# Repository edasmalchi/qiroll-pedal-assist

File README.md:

# qiroll-pedal-assist
#### External pedal-assist system for Qiroll ebike kit, implemented with CMOS digital logic

So I got this Qiroll friction-drive ebike kit  to put on my commuter bike. I'd reccomend the [pro](https://www.aliexpress.com/item/1005002975061464.html) [version](https://www.ebay.com/itm/Electric-Bicycle-E-BIKE-Conversion-Kit-QiROLL-Friction-Drive-QR-E-PRO-H70/402658347675) (about $600 shipped), but the standard [kit](https://www.aliexpress.com/item/4000366510773.html) (about $450 shipped) is still around. With light pedaling, the pro version on my bike cruises at about 23mph with about 20 miles of range, while the standard kit delivers about 19mph and about 20 miles (with the larger B70 battery).

The lack of any sort of pedal assist bothered me, with the original design you have to hold down a switch to keep the motor on. (It's a simple switch, not a real throttle so the motor is either on or off. There is a way to select between a lower power mode and a higher power mode.)

This project aims to add pedal assist functionality to the Qiroll kit. I'm using this 12-magnet pedal assist [sensor](https://smile.amazon.com/gp/product/B08GY819YF/), although similar products could work too. The project also supports an optional brake sensor, I'm using [this one](https://www.aliexpress.com/item/4000445394702.html) but others likely work as well. Be sure to verify proper operation in case yours works differently.

#### Hardware Mods
* Since my design needs only one button, with single-clicks turning pedal assist on/off and double-clicks switching controller modes (and/or enabling regen), I didn't need the second button in the original Qiroll switch. So I desoldered it, and used the space/wiring for a resistor and an led that lines up nicely with the hole left by taking the button out, letting me see if pedal assist is currently on or off!

* Stripped the insulation and soldered into one of the battery wires to tap power-- should be fine since the pedal assist system uses very little current but be careful not to damage the battery wire itself. Alternatively you could get some of those Amass connectors it uses and make an adaptor.
* Depending on your setup, cable strain at the battery connector seems to be an issue. Reccomend adding extra strain relief here, and consider tapping at the motor connection instead since splicing in another wire with solder does weaken things.

#### Notes
* The sensor I got reads in both directions, so it will trigger on backwards pedaling as well. I don't think this is a big deal, but there may be sensors out there that only read in one direction.
* After much investigation, the power from the Qiroll micro-usb switch port seems to fluctuate quite a bit. So the reliable thing to do is tap into the + side of the battery, using a linear voltage regulator (or buck converter) to drop down the battery voltage.
* ___Use at your own risk! I reccomend extensive testing of whatever implementation you come up with, ensuring your brakes can stop the bike even if the motor sticks on, and having the battery cable within reach to disconnect if necessary!___

#### Progress
* Digital logic version 2.5 builds on 2.2 with usability improvements and taillight connector option
* A simple case for 3d printing
* Stripped-down "simple" digital logic version with through-hole components in case that better meets your needs

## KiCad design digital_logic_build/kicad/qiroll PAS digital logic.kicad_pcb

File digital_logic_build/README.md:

# Digital logic version

Built from some 4000-series CMOS chips, this design also implements pedal assist for the Qiroll kit. Single click turns PAS on/off, double-click turns regen on/off (pro) or changes modes (standard). Triple-click changes modes with the pro, if stopped.

### Notes
* _v2.5 of the PCB version is complete! Board files in the kicad directory are suitable for ordering from JLCPCB, and maybe other sources too. Just track down the parts, do some medium-difficulty surface-mount soldering and you're done! Building on protoboard is also an option, feel free to try a stripped-down version of the design for that or I can help you come up with something_
* Extremely fast double-clicks won't register. But it's easy enough to get a feel for it.
* Per specification, there is 1.5ma of current available for the indicator LED. Please choose color+series resistor to be at or below 1.5ma at 3.3 volts.
* See schematic for design notes

### PCB New Features
* LED flashes under regenerative braking with PAS on or off
* Regen cancel on pedal reliability improved
* Optional brake sensor cancels assist and activates regen braking while mechanical brakes pulled
* Optional accessory connector for a taillight, with brake sensor logic level output for brake light sensing (if taillight supports)

_Illustration of the Qiroll kit without the circuit (top), and how the circuit interfaces (bottom)_

### Build it!
* most parts have a DigiKey or at least a datasheet link if you open the schematic in KiCad and click the "edit symbol fields" icon (4th from right at top)
* also included a csv with part numbers that can be dragged directly into a DigiKey cart, note that it only has quantities for one board (multiply all by 5 if building more/sharing)
* [build video](https://www.youtube.com/watch?v=RqBvx1b3l4g) (sorry for the poor production, feel free to skip around of course!)

### Test it!
* check the board visually for solder joint quality
* _at minimum, verify the battery + voltage is not shorted to anything with a multimeter before connecting to the battery_
* consider functional testing using LEDs to view signals on a breadboard and some sort of square wave generator (you could use a CMOS 555 or 4047B at 3.3v) to stand in for the PAS sensor

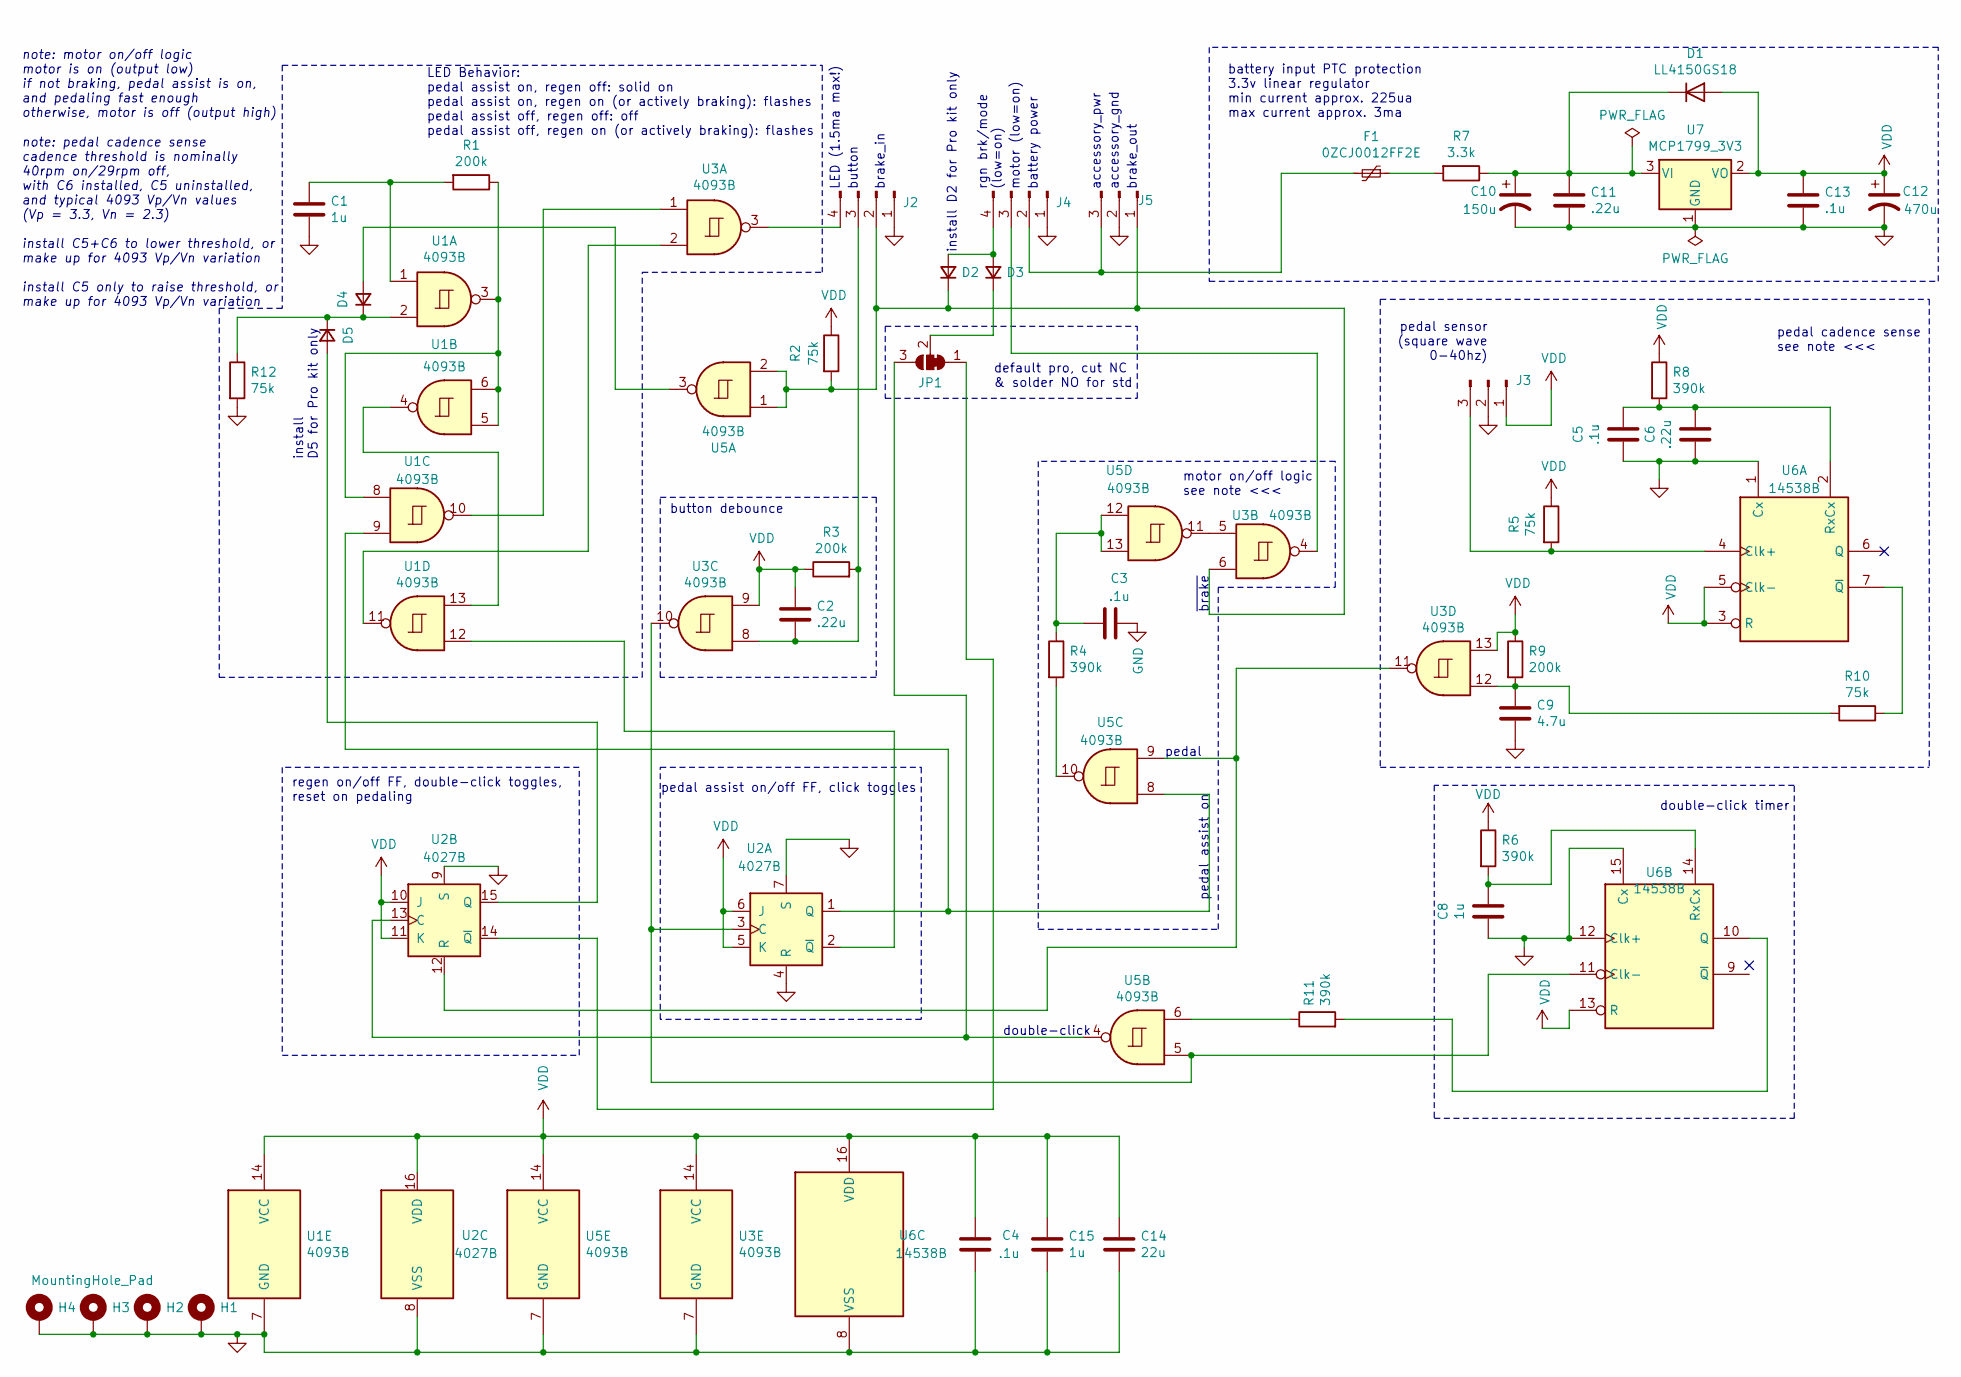
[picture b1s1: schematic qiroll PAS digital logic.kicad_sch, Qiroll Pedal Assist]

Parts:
C1, C8, C15: 1u; C_0603_1608Metric
C2, C6, C11: .22u; C_0603_1608Metric
C3, C4, C5, C13: .1u; C_0603_1608Metric
C9: 4.7u; C_0603_1608Metric
C10: 150u; CP_Radial_D10.0mm_P5.00mm
C12: 470u; CP_Radial_D6.3mm_P2.50mm
C14: 22u; C_0603_1608Metric
D1: LL4150GS18; D_MiniMELF
D2, D3, D4, D5: D; D_SOD-523
F1: 0ZCJ0012FF2E; Fuse_1206_3216Metric
H1, H2, H3, H4: MountingHole_Pad; MountingHole_2.2mm_M2_DIN965_Pad
J2: led_sw1; PinHeader_1x04_P2.54mm_Vertical
J3: accessory; PinHeader_1x03_P2.54mm_Vertical
J4: mode_thr_batt; PinHeader_1x04_P2.54mm_Vertical
J5: 3_pin; PinHeader_1x03_P2.54mm_Vertical
JP1: SolderJumper_3_Bridged12; SolderJumper-3_P1.3mm_Bridged12_RoundedPad1.0x1.5mm_NumberL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
R1, R3, R9: 200k; R_0603_1608Metric
R2, R5, R10, R12: 75k; R_0603_1608Metric
R4, R6, R8, R11: 390k; R_0603_1608Metric
R7: 3.3k; R_0603_1608Metric
U1, U3, U5: 4093B; SOIC-14_3.9x8.7mm_P1.27mm
U2: 4027B; SOIC-16_3.9x9.9mm_P1.27mm
U6: 14538B; SOIC-16_3.9x9.9mm_P1.27mm
U7: MCP1799_3V3; SOT-23

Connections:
GND: C1.2, C3.1, C4.1, C5.2, C6.2, C8.2, C9.2, C10.2, C11.2, C12.2, C13.2, C14.2, C15.2, H1.1, H2.1, H3.1, H4.1, J2.1, J3.2, J4.1, J5.2, R12.2, U1.7 (GND), U2.4 (R), U2.7 (S), U2.8 (VSS), U2.9 (S), U3.7 (GND), U5.7 (GND), U6.1 (Cx), U6.8 (VSS), U6.12 (Clk+), U6.15 (Cx), U7.1 (GND)
unnamed: C1.1, R1.2, U1.1
unnamed: C3.2, R4.1, U5.12, U5.13
unnamed: C9.1, R9.2, R10.2, U3.12
unnamed: C10.1, C11.1, D1.1 (K), R7.1, U7.3 (VI)
unnamed: D2.2 (A), D3.2 (A), J4.4
unnamed: D2.1 (K), J2.2, J5.1, R2.2, U3.6, U5.1, U5.2
unnamed: D3.1 (K), JP1.2 (C)
unnamed: D4.2 (A), U5.3
unnamed: D4.1 (K), D5.1 (K), R12.1, U1.2
unnamed: D5.2 (A), U2.15 (Q)
unnamed: F1.1, R7.2
unnamed: C2.2, J2.3, R3.2, U3.8
unnamed: J2.4, U3.3
unnamed: J3.3, R5.2, U6.4 (Clk+)
unnamed: F1.2, J4.2, J5.3
unnamed: J4.3, U3.4
unnamed: JP1.1 (A), U2.14 (~Q)
unnamed: JP1.3 (B), U2.13 (C), U5.4
unnamed: R1.1, U1.3, U1.5, U1.6, U1.8
unnamed: R4.2, U5.10
unnamed: R11.1, U5.6
unnamed: U1.10, U3.1
unnamed: U1.11, U3.2
unnamed: U1.4, U1.13
unnamed: U2.3 (C), U3.10, U5.5, U6.11 (Clk-)
unnamed: U1.9, U2.1 (Q), U5.8
unnamed: U1.12, U2.2 (~Q)
unnamed: U2.12 (R), U3.11, U5.9
unnamed: U3.5, U5.11
unnamed: C5.1, C6.1, R8.2, U6.2 (RxCx)
unnamed: R10.1, U6.7 (~Q)
unnamed: R11.2, U6.10 (Q)
unnamed: C8.1, R6.2, U6.14 (RxCx)
VDD: C2.1, C4.2, C12.1, C13.1, C14.1, C15.1, D1.2 (A), J3.1, R2.1, R3.1, R5.1, R6.1, R8.1, R9.1, U1.14 (VCC), U2.5 (K), U2.6 (J), U2.10 (J), U2.11 (K), U2.16 (VDD), U3.9, U3.13, U3.14 (VCC), U5.14 (VCC), U6.3 (R), U6.5 (Clk-), U6.13 (R), U6.16 (VDD), U7.2 (VO)

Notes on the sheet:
motor on/off logic see note <<<
regen on/off FF, double-click toggles, reset on pedaling
note: motor on/off logic motor is on (output low) if not braking, pedal assist is on, and pedaling fast enough otherwise, motor is off (output high)
pedal sensor (square wave 0-40hz)
rgn brk/mode (low=on)
double-click
pedal cadence sense see note <<<
accessory_gnd
button
pedal
button debounce
motor (low=on)
default pro, cut NC & solder NO for std
brake_in
pedal assist on/off FF, click toggles
LED (1.5ma max!)
battery power
install D5 for Pro kit only
install D2 for Pro kit only
double-click timer
~{brake}
brake_out
LED Behavior: pedal assist on, regen off: solid on pedal assist on, regen on (or actively braking): flashes pedal assist off, regen off: off pedal assist off, regen on (or actively braking): flashes
note: pedal cadence sense cadence threshold is nominally 40rpm on/29rpm off, with C6 installed, C5 uninstalled, and typical 4093 Vp/Vn values (Vp = 3.3, Vn = 2.3) install C5+C6 to lower threshold, or make up for 4093 Vp/Vn variation install C5 only to raise threshold, or make up for 4093 Vp/Vn vari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
pedal assist on
battery input PTC protection 3.3v linear regulator min current approx. 225ua max current approx. 3ma
accessory_pwr

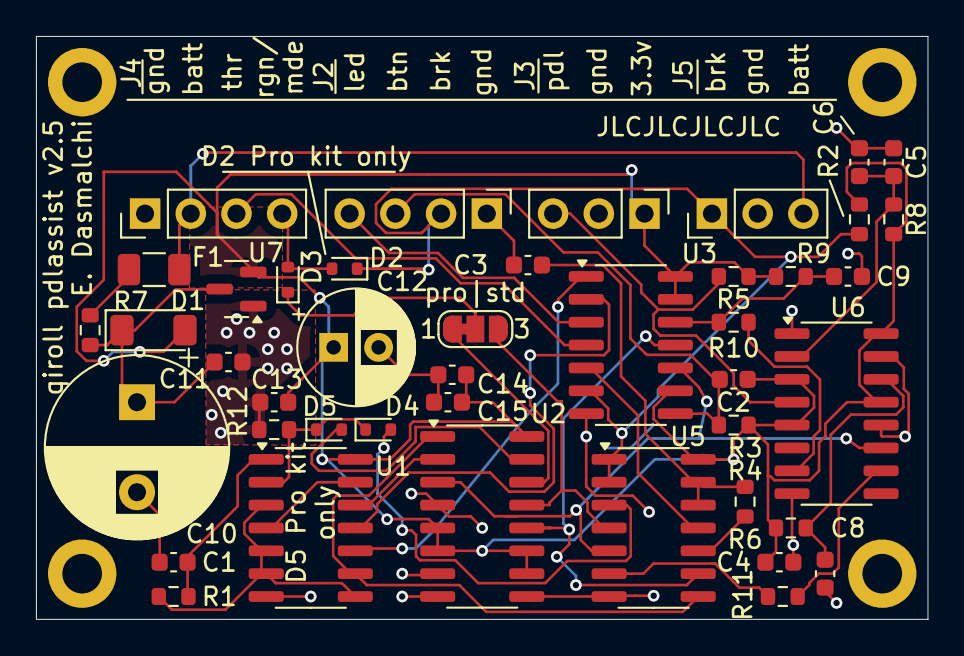
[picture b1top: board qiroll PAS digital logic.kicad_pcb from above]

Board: 2 copper layers, 49.5 x 32.4 mm, 47 parts (0 on the bottom side), 35 nets.

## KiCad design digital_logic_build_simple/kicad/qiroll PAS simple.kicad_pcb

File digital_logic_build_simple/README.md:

# Digital logic version (simple)

Built from some 4000-series CMOS chips, this design implements pedal assist for the Qiroll kit. Single click turns PAS on/off, double-click turns regen on/off (pro) or changes modes (standard). Triple-click changes modes with the pro, must be stopped.

### Notes
* Does not support regen LED flash or latching regen on the Pro kit (brake sensor simple regen still an option)

_Illustration of the Qiroll kit without the circuit (top), and how the circuit interfaces (bottom)_

### Build it!
* most parts have a DigiKey or at least a datasheet link if you open the schematic in KiCad and click the "edit symbol fields" icon (4th from right at top)

### Test it!
* check the board visually for solder joint quality
* _at minimum, verify the battery + voltage is not shorted to anything with a multimeter before connecting to the battery_
* consider functional testing using LEDs to view signals on a breadboard and some sort of square wave generator (you could use a CMOS 555 or 4047B at 3.3v) to stand in for the PAS sensor

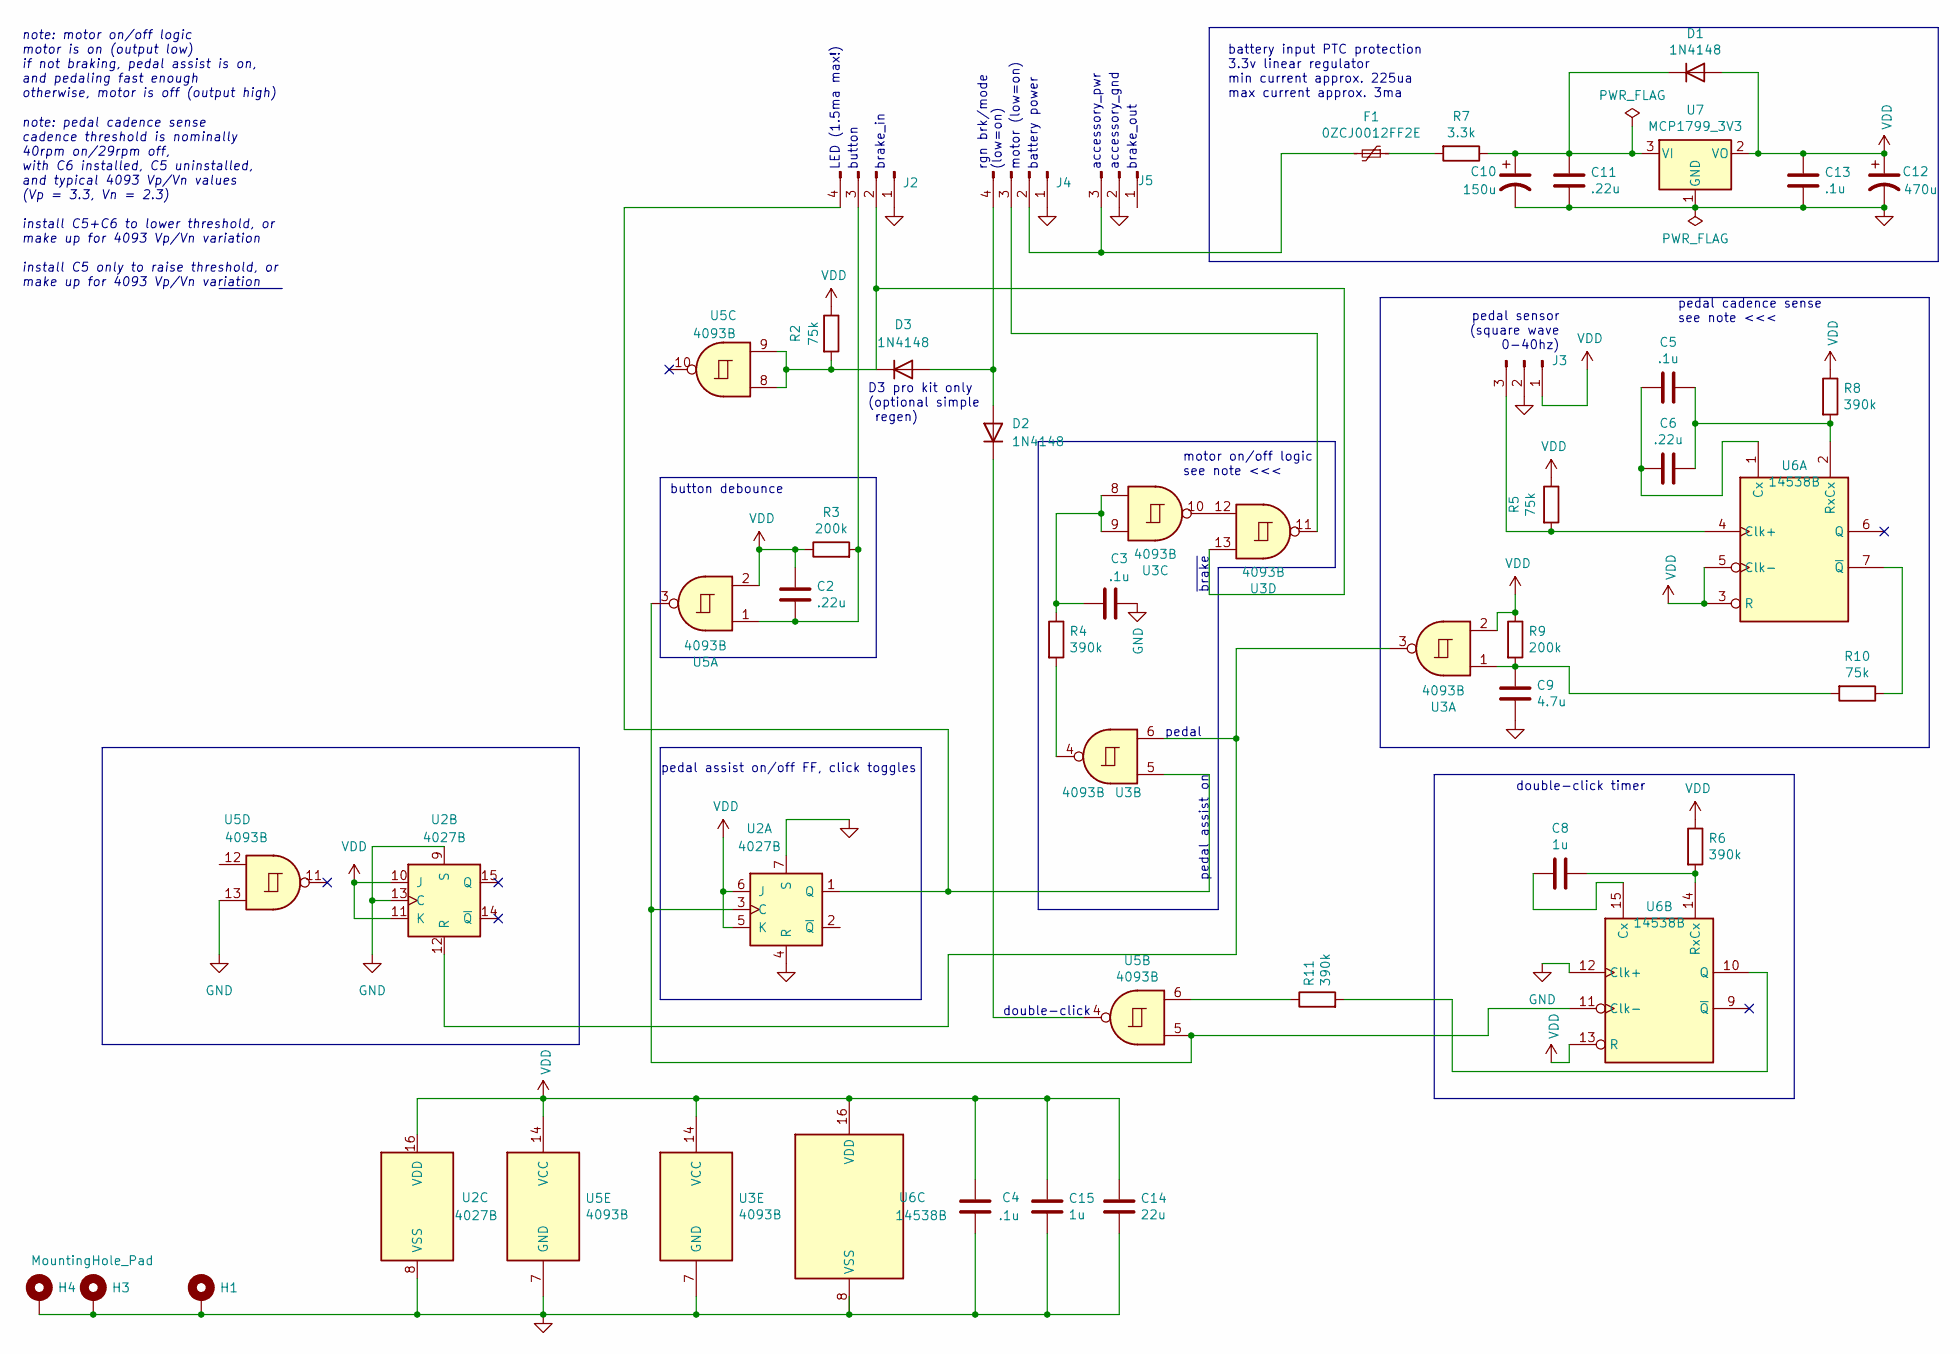
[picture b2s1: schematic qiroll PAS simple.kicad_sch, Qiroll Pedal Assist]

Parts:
C2, C6, C11: .22u; C_Rect_L4.6mm_W3.0mm_P2.50mm_MKS02_FKP02
C3, C4, C5, C13: .1u; C_Rect_L4.6mm_W3.0mm_P2.50mm_MKS02_FKP02
C8, C15: 1u; C_Rect_L4.6mm_W3.0mm_P2.50mm_MKS02_FKP02
C9: 4.7u; C_Rect_L4.6mm_W3.0mm_P2.50mm_MKS02_FKP02
C10: 150u; R_Axial_DIN0204_L3.6mm_D1.6mm_P5.08mm_Vertical
C12: 470u; CP_Radial_D6.3mm_P2.50mm
C14: 22u; CP_Radial_D5.0mm_P2.00mm
D1: 1N4148; D_DO-35_SOD27_P3.81mm_Vertical_AnodeUp
D2, D3: 1N4148; D_DO-35_SOD27_P7.62mm_Horizontal
F1: 0ZCJ0012FF2E; R_Axial_DIN0309_L9.0mm_D3.2mm_P5.08mm_Vertical
H1, H3, H4: MountingHole_Pad; MountingHole_2.2mm_M2_DIN965_Pad
J2: led_sw1; PinHeader_1x04_P2.54mm_Vertical
J3: accessory; PinHeader_1x03_P2.54mm_Vertical
J4: mode_thr_batt; PinHeader_1x04_P2.54mm_Vertical
J5: 3_pin; PinHeader_1x03_P2.54mm_Vertical
R2: 75k; R_Axial_DIN0207_L6.3mm_D2.5mm_P7.62mm_Horizontal
R3, R9: 200k; R_Axial_DIN0207_L6.3mm_D2.5mm_P2.54mm_Vertical
R4, R6, R8, R11: 390k; R_Axial_DIN0207_L6.3mm_D2.5mm_P2.54mm_Vertical
R5, R10: 75k; R_Axial_DIN0207_L6.3mm_D2.5mm_P2.54mm_Vertical
R7: 3.3k; R_Axial_DIN0207_L6.3mm_D2.5mm_P2.54mm_Vertical
U2: 4027B; DIP-16_W7.62mm
U3, U5: 4093B; DIP-14_W7.62mm
U6: 14538B; DIP-16_W7.62mm
U7: MCP1799_3V3; TO-92

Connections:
GND: C3.1, C4.1, C9.2, C10.2, C11.2, C12.2, C13.2, C14.2, C15.2, H1.1, H3.1, H4.1, J2.1, J3.2, J4.1, J5.2, U2.4 (R), U2.7 (S), U2.8 (VSS), U2.9 (S), U2.13 (C), U3.7 (GND), U5.7 (GND), U5.13, U6.8 (VSS), U6.12 (Clk+), U7.1 (GND)
unnamed: C2.2, J2.3, R3.2, U5.1
unnamed: C3.2, R4.1, U3.8, U3.9
unnamed: C5.1, C6.1, R8.2, U6.2 (RxCx)
unnamed: C5.2, C6.2, U6.1 (Cx)
unnamed: C8.1, R6.2, U6.14 (RxCx)
unnamed: C8.2, U6.15 (Cx)
unnamed: C9.1, R9.2, R10.2, U3.1
unnamed: C10.1, C11.1, D1.1 (K), R7.1, U7.3 (VI)
unnamed: D2.1 (K), U5.4
unnamed: D2.2 (A), D3.2 (A), J4.4
unnamed: D3.1 (K), J2.2, R2.2, U3.13, U5.8, U5.9
unnamed: F1.1, R7.2
unnamed: F1.2, J4.2, J5.3
unnamed: J2.4, U2.1 (Q), U3.5
unnamed: J3.3, R5.2, U6.4 (Clk+)
unnamed: J4.3, U3.11
unnamed: R4.2, U3.4
unnamed: R10.1, U6.7 (~Q)
unnamed: R11.1, U5.6
unnamed: R11.2, U6.10 (Q)
unnamed: U2.3 (C), U5.3, U5.5, U6.11 (Clk-)
unnamed: U2.12 (R), U3.3, U3.6
unnamed: U3.10, U3.12

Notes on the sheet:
motor on/off logic see note <<<
note: motor on/off logic motor is on (output low) if not braking, pedal assist is on, and pedaling fast enough otherwise, motor is off (output high)
pedal sensor (square wave 0-40hz)
rgn brk/mode (low=on)
double-click
pedal cadence sense see note <<<
accessory_gnd
button
pedal
button debounce
motor (low=on)
D3 pro kit only (optional simple regen)
brake_in
pedal assist on/off FF, click toggles
LED (1.5ma max!)
battery power
double-click timer
~{brake}
brake_out
note: pedal cadence sense cadence threshold is nominally 40rpm on/29rpm off, with C6 installed, C5 uninstalled, and typical 4093 Vp/Vn values (Vp = 3.3, Vn = 2.3) install C5+C6 to lower threshold, or make up for 4093 Vp/Vn variation install C5 only to raise threshold, or make up for 4093 Vp/Vn vari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
pedal assist on
battery input PTC protection 3.3v linear regulator min current approx. 225ua max current approx. 3ma
accessory_pwr

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
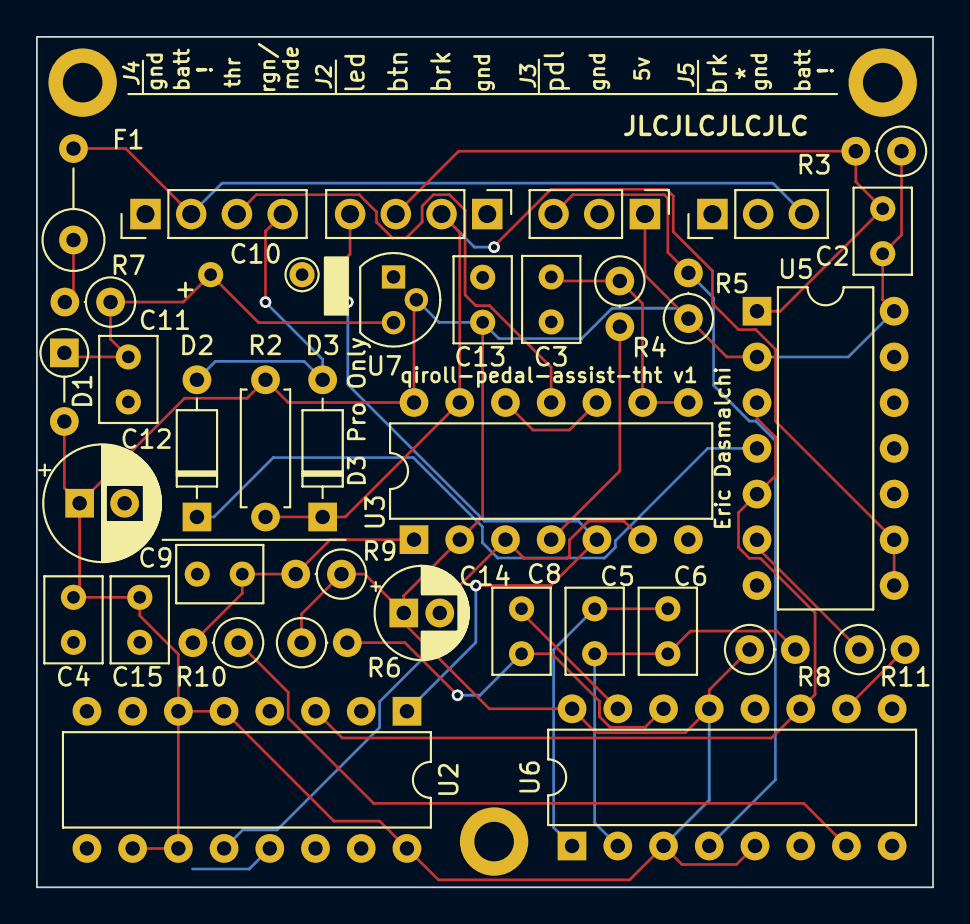
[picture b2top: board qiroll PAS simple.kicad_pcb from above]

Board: 2 copper layers, 49.8 x 47.2 mm, 39 parts (0 on the bottom side), 25 nets.

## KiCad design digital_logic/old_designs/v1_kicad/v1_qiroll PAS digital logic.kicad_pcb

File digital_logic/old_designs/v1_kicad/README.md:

#### Design notes for Version 1

### Important: ###

_If you ordered PCBs with the gerber files provided here, or in the main digital logic folder from June 28, 2021 to July 17, 2021, your boards require rework for safety and usability_

(to the best of my knowledge however, nobody did)

#### Rework tasks
* Cut trace connecting U6 pad 6 to U2 pad 10! (fixes a safety issue where a brake sensor activation would have stuck the motor *on*!) Instead, connect U6 pad 6 to VCC.
* Add pulldown resistor from J4 pin 1 to GND (10k is fine)
* Add protection diode: anode to VCC and cathode to U5 pin 1 (1N4003 or higher rated, I used 1N4007)

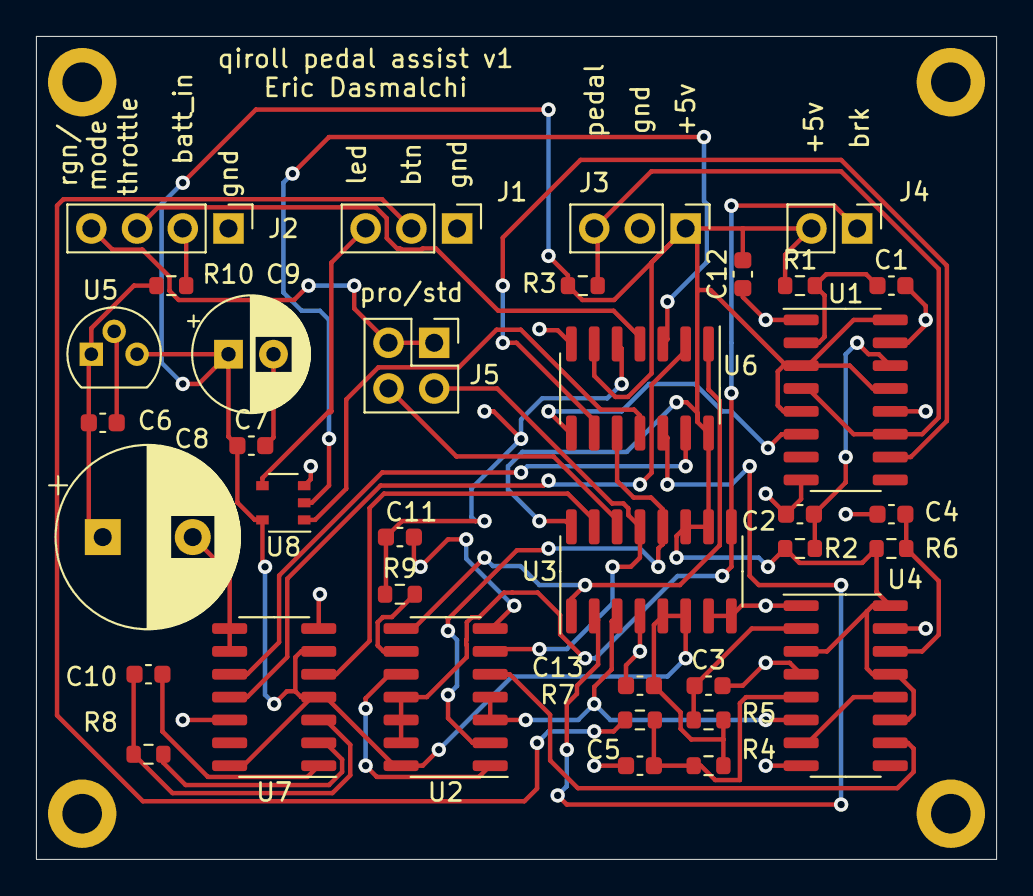
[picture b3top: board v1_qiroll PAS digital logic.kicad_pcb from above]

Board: 2 copper layers, 53.3 x 45.7 mm, 40 parts (0 on the bottom side), 36 nets.

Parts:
C1, C2, C4, C5, C11: 1u; C_0603_1608Metric
C3, C6, C10: 0.47u; C_0603_1608Metric
C7, C12, C13: .1u; C_0603_1608Metric
C8: 150u; CP_Radial_D10.0mm_P5.00mm
C9: 200u; CP_Radial_D6.3mm_P2.50mm
H1, H2, H3, H4: MountingHole_Pad; MountingHole_2.2mm_M2_DIN965_Pad
J1: led_sw1; PinHeader_1x03_P2.54mm_Vertical
J2: mode_thr_batt; PinHeader_1x04_P2.54mm_Vertical
J3: pas_sense; PinHeader_1x03_P2.54mm_Vertical
J4: brk_sense; PinHeader_1x02_P2.54mm_Vertical
J5: jumper; PinHeader_2x02_P2.54mm_Vertical
R1, R2: 200k; R_0603_1608Metric
R3, R7: 10k; R_0603_1608Metric
R4, R5, R8: 100k; R_0603_1608Metric
R6: 392k; R_0603_1608Metric
R9: 392K; R_0603_1608Metric
R10: 1.6k; R_0603_1608Metric
U1, U4: 14538; SOIC-16_3.9x9.9mm_P1.27mm
U2: 4023; SOIC-14_3.9x8.7mm_P1.27mm
U3: 4027; SOIC-16_3.9x9.9mm_P1.27mm
U5: L7805; TO-92
U6: 4081; SOIC-14_3.9x8.7mm_P1.27mm
U7: 4047; SOIC-14_3.9x8.7mm_P1.27mm
U8: 74VHC1G32; TSOP-5_1.65x3.05mm_P0.95mm

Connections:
BRK: J4.1, U2.11, U2.12, U2.13, U3.9
GND: C1.2, C2.2, C3.2, C4.2, C5.1, C6.2, C7.2, C8.2, C9.2, C11.1, C12.1, C13.1, H1.1, H2.1, H3.1, H4.1, J1.1, J2.1, J3.2, U1.1, U1.8, U1.12, U1.15, U2.7, U3.4, U3.7, U3.8, U4.1, U4.4, U4.8, U4.15, U5.2, U6.7, U7.7, U7.8, U7.9, U7.12, U8.3
unnamed: C1.1, R1.2, U1.2
unnamed: C2.1, R2.2, U1.14
unnamed: C3.1, R5.2, U4.2
unnamed: C4.1, R6.2, U4.14
unnamed: C5.2, R4.2, R7.2, U4.5
unnamed: C6.1, C8.1, R10.1, U5.1
unnamed: C10.1, U7.1
unnamed: C10.2, R8.1, U7.3
unnamed: C11.2, R9.1, U6.5
unnamed: J1.2, R7.1
unnamed: J1.3, U8.4
unnamed: J2.2, R10.2
unnamed: J2.3, U6.4
unnamed: J2.4, J5.1, J5.3
unnamed: J3.3, R3.2, U1.4, U1.11
unnamed: J5.2, U2.6, U3.13
unnamed: J5.4, U3.14
unnamed: R8.2, U7.2
unnamed: R9.2, U2.9
unnamed: U1.6, U6.8
unnamed: U1.10, U6.9
unnamed: U2.1, U2.10
unnamed: U2.3, U2.4, U3.3, U4.6
unnamed: U2.5, U4.10
unnamed: U3.15, U7.5
unnamed: U4.7, U4.12
unnamed: U6.3, U8.2
unnamed: U6.13, U7.10
PAS_OFF: U3.2, U6.12
PAS_ON: U2.8, U3.1, U6.1
PEDAL: U2.2, U3.12, U6.10
RGN_FLSH: U6.2, U7.11
RGN_FLSH_2: U6.11, U8.1
VCC: C7.1, C9.1, C12.2, C13.2, J3.1, J4.2, R1.1, R2.1, R3.1, R4.1, R5.1, R6.1, U1.3, U1.5, U1.13, U1.16, U2.14, U3.5, U3.6, U3.10, U3.11, U3.16, U4.3, U4.11, U4.13, U4.16, U5.3, U6.6, U6.14, U7.4, U7.6, U7.14, U8.5

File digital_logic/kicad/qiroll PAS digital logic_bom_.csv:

Component,Description,Part,References,Value,Footprint,Quantity Per PCB,Datasheet
1,Unpolarized capacitor,C,C7 C12 C13,.1u,C_0603_1608Metric,3,https://www.digikey.com/en/products/detail/taiyo-yuden/EMK10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 
2,Unpolarized capacitor,C,C3 C6 C10,0.47u,C_0603_1608Metric,3,https://www.digikey.com/en/products/detail/tdk-corporation/C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
3,Unpolarized capacitor,C,C1 C2 C4 C5 C11,1u,C_0603_1608Metric,5,https://www.digikey.com/en/products/detail/tdk-corporation/C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
4,"Polarized capacitor, US symbol",CP1,C8,150u,CP_Radial_D10.0mm_P5.00mm,1,https://www.digikey.com/en/products/detail/nichicon/UPW1H151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
5,"Polarized capacitor, US symbol",CP1,C9,200u,CP_Radial_D6.3mm_P2.50mm,1,https://www.digikey.com/en/products/detail/rubycon/8AX200MEF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
6,"Generic connector, single row, 01x02, script generated (kicad-library-utils/schlib/autogen/connector/)",Conn_01x02_Male,J4,brk_sense,PinHeader_1x02_P2.54mm_Vertical,1,~
7,"Generic connector, double row, 02x02, odd/even pin numbering scheme (row 1 odd numbers, row 2 even numbers), script generated (kicad-library-utils/schlib/autogen/connector/)",Conn_02x02_Odd_Even,J5,jumper,PinHeader_2x02_P2.54mm_Vertical,1,~
8,"Generic connector, single row, 01x03, script generated (kicad-library-utils/schlib/autogen/connector/)",Conn_01x03_Male,J1 J3,led_sw1,PinHeader_1x03_P2.54mm_Vertical,2,~
9,"Generic connector, single row, 01x04, script generated (kicad-library-utils/schlib/autogen/connector/)",Conn_01x04_Male,J2,mode_thr_batt,PinHeader_1x04_P2.54mm_Vertical,1,~
10,Resistor,R,R10,1.6k,R_0603_1608Metric,1,~
11,Resistor,R,R3 R7,10k,R_0603_1608Metric,2,~
12,Resistor,R,R4 R5 R8,100k,R_0603_1608Metric,3,~
13,Resistor,R,R1 R2,200k,R_0603_1608Metric,2,~
14,Resistor,R,R6 R9,392k,R_0603_1608Metric,2,~
15,Monostable,14538,U1 U4,14538,SOIC-16_3.9x9.9mm_P1.27mm,2,https://www.onsemi.com/pub/Collateral/MC14538B-D.PDF
16,Triple Nand 3 inputs,4023,U2,4023,SOIC-14_3.9x8.7mm_P1.27mm,1,http://www.intersil.com/content/dam/Intersil/documents/cd40/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
17,"Dual JK FlipFlop, set & reset",4027,U3,4027,SOIC-16_3.9x9.9mm_P1.27mm,1,http://www.intersil.com/content/dam/Intersil/documents/cd40/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
18,Monostable/Astable Multivibrator,4047,U7,4047,SOIC-14_3.9x8.7mm_P1.27mm,1,https://www.ti.com/lit/ds/symlink/cd4047b.pdf
19,Quad And 2 inputs,4081,U6,4081,SOIC-14_3.9x8.7mm_P1.27mm,1,http://www.intersil.com/content/dam/Intersil/documents/cd40/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
20,"Single OR Gate, Low-Voltage CMOS",74AHC1G32,U8,74VHC1G32,TSOP-5_1.65x3.05mm_P0.95mm,1,https://www.digikey.com/en/products/detail/on-semiconductor/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
21,"Positive 1.5A 35V Linear Regulator, Fixed Output 5V, TO-220/TO-263/TO-252",L7805,U5,L7805,TO-92,1,http://www.st.com/content/ccc/resource/technical/document/da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





Component Groups:,21
Component Count:,36
Fitted Components:,36
Number of PCBs:,1
Total components:,36
Schematic Version:,
Schematic Date:,
PCB Variant:,default
BoM Date:,"Tuesday, June 29, 2021 at 11:20:10 AM"
Schematic Source:,qiroll PAS digital logic.sch
KiCad Version:,Eeschema (5.1.10-1-10_14)

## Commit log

2021-01-16 add early version attiny85 sketch
2021-01-16 placed sketch in folder to placate Arduino IDE
2021-01-17 bench-tested demo on digispark/attiny85, using pulse duration method
2021-01-17 update comments
2021-01-17 incomplete frequency-counter version
2021-01-17 fixed bug preventing LED from turning off after pas mode turned off
2021-01-18 improve code legibility
2021-01-18 fix find/replace error
2021-01-20 working on-bike test, still have to find right timing for cadence cutoff
2021-01-23 works on-bike, double-clk buggy
2021-01-26 first version tested on-bike, mostly working
2021-01-26 Update attiny85_digispark.ino
    clarify/fix triple-click mode change
2021-02-04 as-working on-bike with stripboard connector adaptor
2021-02-21 add aggressive debouncing to attiny85 version, kicad files for digital logic version (incomplete)
2021-02-21 add kicad files for digital logic version (unfinished)
2021-02-21 digital logic prototype kicad schematic, complete but untested
2021-02-21 fix schematic, export to png
2021-02-21 move kicad cache file
2021-02-22 fix arduino mode switch bug
2021-03-28 minor code update
2021-03-28 add rc debounce, decoupling
2021-03-28 update r1r2 values
2021-04-01 annotate schematic, voltage regulator, photos
2021-04-02 one last photo
2021-04-05 fix schematic errors, swap 4023 units for ease of assembly
2021-04-05 crop schematic
2021-04-05 match new schematic
2021-04-05 one more thing
2021-06-17 add electrolytic caps for stability
2021-06-20 add voltage reg caps to schematic.png, start work on v2
2021-06-28 pcb version 1, new features
2021-07-02 add brake sensor pulldown, incomplete BOM
2021-07-02 relabel old shcematic
2021-07-02 remove v1 gerbers
2021-07-03 add ptc and protection diode for voltage reg
2021-07-12 revised pcb w/ ptc, protection diode, revised c11 value
2021-07-14 pcb revision, add circuit sim, old kicad files to reference for v1 board repairs
2021-07-17 add old design safety notes, delete faulty gerbers
2021-07-17 actually add notes
2021-07-20 more Schmitt triggers\!
2021-07-20 trial component placement
2021-07-23 v2 PCB for review/manufacture
2021-07-23 add v2 gerbers, pending review
2021-07-23 readme updates
2021-07-30 v2 PCB for production
2021-09-04 add case CAD files, 3d print instructions for Creality Ender
2021-09-04 move images to folder
2021-09-04 update photos
2021-09-04 schematic naming
2021-10-01 resize images
2021-10-16 pcb version 2.2, hopefully fixes brake input/mode instablity
2021-10-16 add v2.2 schematic
2021-10-18 remove old files, add new schematic
2021-10-18 actually add schematic
2021-10-20 fix brake label, a more connected ground plane
2021-11-07 nicer photo
2021-11-20 remove arduino
2021-11-20 new folder
2021-11-20 remove old
2021-12-15 version 2.5
2021-12-15 gerbers and schematic
2021-12-15 remove old sch
2021-12-16 better bike photo
2021-12-16 better bike photo2
2021-12-16 more photos
2021-12-16 block diagram
2021-12-16 add digikey bom
2021-12-17 clarify silkscreen
2021-12-18 even tidier schematic
2022-02-17 add simple, update main pcb to KiCad 6
2022-02-17 fix simple schematic, delete old files
2024-06-12 update pcb to new kicad
2024-06-26 revise footprints
2024-06-26 bigger silkscreen
2024-06-27 new gerbers
